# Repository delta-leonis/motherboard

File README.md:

# `motherboard`
> generic motherboard for robotic applications

The motherboard has seven identical slots for  modules which
are connected to a single CPU module slot which has up to seventy general purpose
inputs and outputs (GPIO), as well as , , and  communication buses.
The Motherboard also supplies each module with a direct battery connection
and additionally regulated  and  lines.

## Repository Contents
  * **/bom** - Bill of Materials csv files
  * **/design** - Autodesk Eagle design files & support library
  * **/gerbers** - Rendered Gerber RS_274x & Excellon files
  * **/images** - README image files
  * **/license** - License info

## Version History
  * [v1.0]() - Initial release - *January 2017*
  * [v1.1]() - Unreleased Version
  * [v1.2]() - Second production version - *April 2017*
  * v1.3 - Current version - *June 2017*

## Block Diagram

## Copyright

This work is licensed under a [Creative Commons Attribution-NonCommercial-ShareAlike 4.0 International License](https://creativecommons.org/licenses/by-nc-sa/4.0/legalcode)

**Attribution** — You must give [appropriate credit](/license/credit.md), provide a link to the license, and
[indicate if changes were made](https://wiki.creativecommons.org/License_Versions#Modifications_and_adaptations_must_be_marked_as_such).
You may do so in any reasonable manner, but not in any way that suggests the licensor endorses you or your use.

**NonCommercial** — You may not use the material for [commercial purposes]().

**ShareAlike** — If you remix, transform, or build upon the material, you must distribute your contributions under the [same license](https://creativecommons.org/licenses/by-nc-sa/4.0/legalcode) as the original.

If you have any questions or concerns on licensing, please contact [seifmegahed@me.com](mailto:seifmegahed@me.com)

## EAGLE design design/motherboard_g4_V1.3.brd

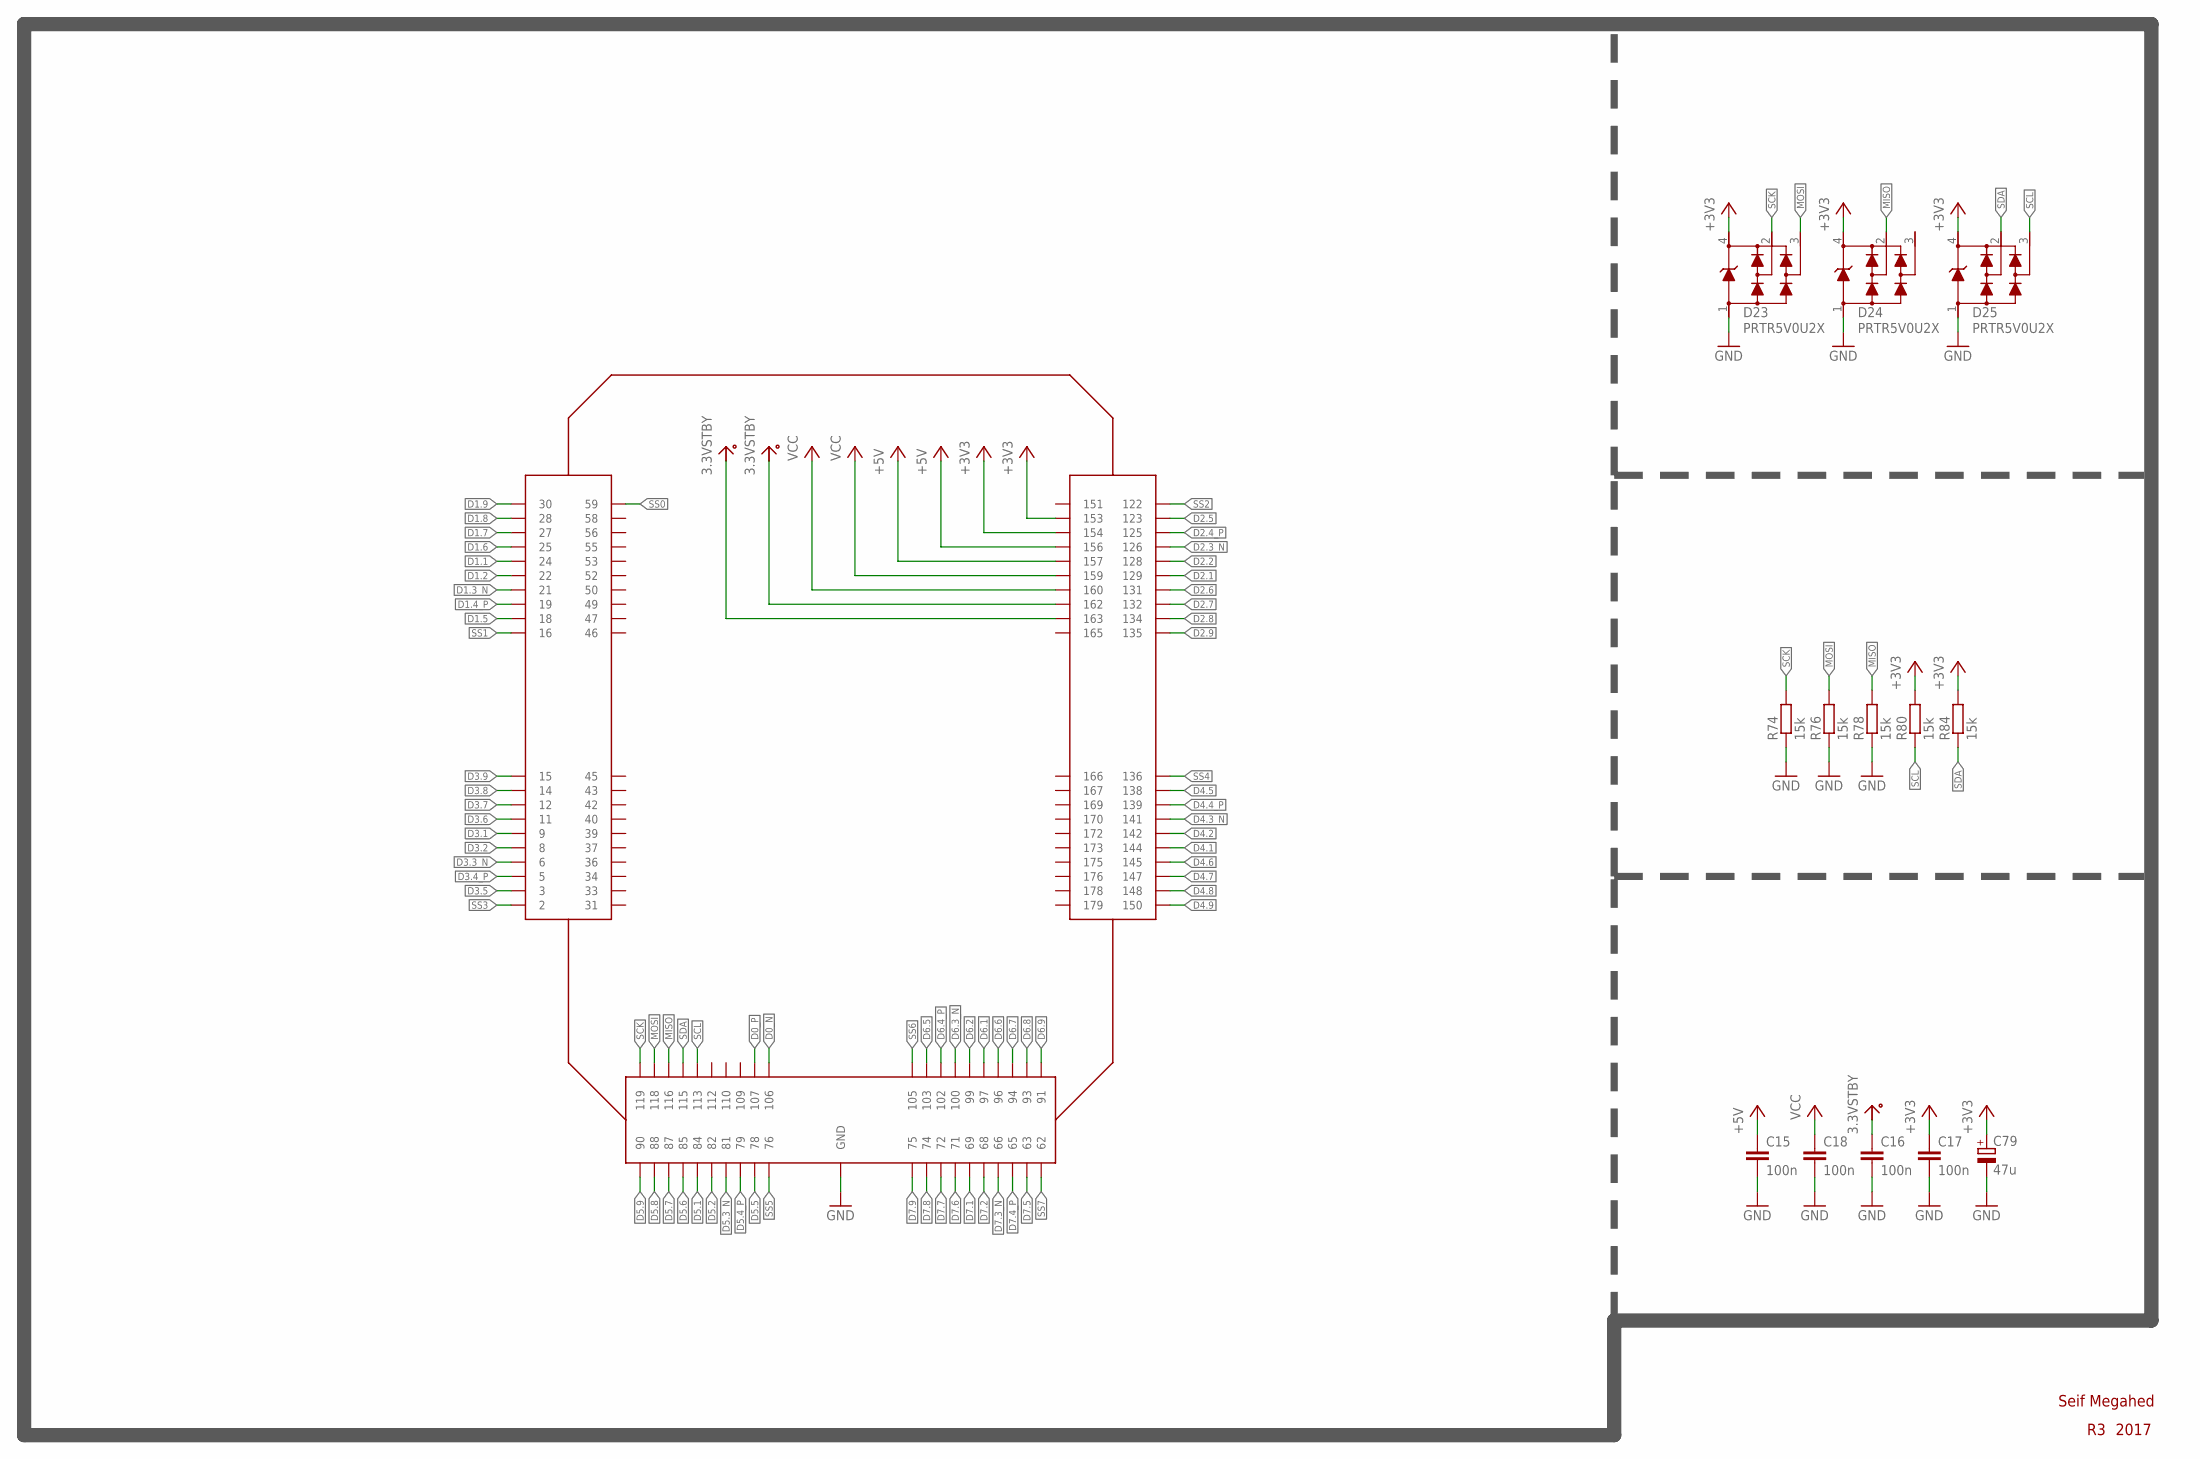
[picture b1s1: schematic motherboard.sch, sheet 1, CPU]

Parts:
C15, C16, C17, C18: 100n; CAP_0603
C79: 47u; PANASONIC_C
D23, D24, D25: PRTR5V0U2X; SOT143B
R74, R76, R78, R80, R84: 15k; RES_0603
U$4: SSH-G4-CPUDOCK; SSH-CPU-DOCK

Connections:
+3V3: C17.1, C79.+, D23.4, D24.4, D25.4, R80.2, R84.2, U$4.153, U$4.154; also elsewhere on the board
+5V: C15.1, U$4.156, U$4.157; also elsewhere on the board
D0_N: U$4.106; also elsewhere on the board
D0_P: U$4.107; also elsewhere on the board
D1.1: U$4.24; also elsewhere on the board
D1.2: U$4.22; also elsewhere on the board
D1.3_N: U$4.21; also elsewhere on the board
D1.4_P: U$4.19; also elsewhere on the board
D1.5: U$4.18; also elsewhere on the board
D1.6: U$4.25; also elsewhere on the board
D1.7: U$4.27; also elsewhere on the board
D1.8: U$4.28; also elsewhere on the board
D1.9: U$4.30; also elsewhere on the board
D2.1: U$4.129; also elsewhere on the board
D2.2: U$4.128; also elsewhere on the board
D2.3_N: U$4.126; also elsewhere on the board
D2.4_P: U$4.125; also elsewhere on the board
D2.5: U$4.123; also elsewhere on the board
D2.6: U$4.131; also elsewhere on the board
D2.7: U$4.132; also elsewhere on the board
D2.8: U$4.134; also elsewhere on the board
D2.9: U$4.135; also elsewhere on the board
D3.1: U$4.9; also elsewhere on the board
D3.2: U$4.8; also elsewhere on the board
D3.3_N: U$4.6; also elsewhere on the board
D3.4_P: U$4.5; also elsewhere on the board
D3.5: U$4.3; also elsewhere on the board
D3.6: U$4.11; also elsewhere on the board
D3.7: U$4.12; also elsewhere on the board
D3.8: U$4.14; also elsewhere on the board
D3.9: U$4.15; also elsewhere on the board
D4.1: U$4.144; also elsewhere on the board
D4.2: U$4.142; also elsewhere on the board
D4.3_N: U$4.141; also elsewhere on the board
D4.4_P: U$4.139; also elsewhere on the board
D4.5: U$4.138; also elsewhere on the board
D4.6: U$4.145; also elsewhere on the board
D4.7: U$4.147; also elsewhere on the board
D4.8: U$4.148; also elsewhere on the board
D4.9: U$4.150; also elsewhere on the board
D5.1: U$4.84; also elsewhere on the board
D5.2: U$4.82; also elsewhere on the board
D5.3_N: U$4.81; also elsewhere on the board
D5.4_P: U$4.79; also elsewhere on the board
D5.5: U$4.78; also elsewhere on the board
D5.6: U$4.85; also elsewhere on the board
D5.7: U$4.87; also elsewhere on the board
D5.8: U$4.88; also elsewhere on the board
D5.9: U$4.90; also elsewhere on the board
D6.1: U$4.97; also elsewhere on the board
D6.2: U$4.99; also elsewhere on the board
D6.3_N: U$4.100; also elsewhere on the board
D6.4_P: U$4.102; also elsewhere on the board
D6.5: U$4.103; also elsewhere on the board
D6.6: U$4.96; also elsewhere on the board
D6.7: U$4.94; also elsewhere on the board
D6.8: U$4.93; also elsewhere on the board
D6.9: U$4.91; also elsewhere on the board
D7.1: U$4.69; also elsewhere on the board
D7.2: U$4.68; also elsewhere on the board
D7.3_N: U$4.66; also elsewhere on the board
D7.4_P: U$4.65; also elsewhere on the board
D7.5: U$4.63; also elsewhere on the board
D7.6: U$4.71; also elsewhere on the board
D7.7: U$4.72; also elsewhere on the board
D7.8: U$4.74; also elsewhere on the board
D7.9: U$4.75; also elsewhere on the board
GND: C15.2, C16.2, C17.2, C18.2, C79.-, D23.1, D24.1, D25.1, R74.1, R76.1, R78.1, U$4.1 (GND), U$4.4 (GND), U$4.7 (GND), U$4.10 (GND), U$4.13 (GND), U$4.17 (GND), U$4.20 (GND), U$4.23 (GND), U$4.26 (GND), U$4.29 (GND), U$4.32 (GND), U$4.35 (GND), U$4.38 (GND), U$4.41 (GND), U$4.44 (GND), U$4.48 (GND), U$4.51 (GND), U$4.54 (GND), U$4.57 (GND), U$4.60 (GND), U$4.61 (GND), U$4.64 (GND), U$4.67 (GND), U$4.70 (GND), U$4.73 (GND), U$4.77 (GND), U$4.80 (GND), U$4.83 (GND), U$4.86 (GND), U$4.89 (GND), U$4.92 (GND), U$4.95 (GND), U$4.98 (GND), U$4.101 (GND), U$4.104 (GND), U$4.108 (GND), U$4.111 (GND), U$4.114 (GND), U$4.117 (GND), U$4.120 (GND), U$4.121 (GND), U$4.124 (GND), U$4.127 (GND), U$4.130 (GND), U$4.133 (GND), U$4.137 (GND), U$4.140 (GND), U$4.143 (GND), U$4.146 (GND), U$4.149 (GND), U$4.152 (GND), U$4.155 (GND), U$4.158 (GND), U$4.161 (GND), U$4.164 (GND), U$4.168 (GND), U$4.171 (GND), U$4.174 (GND), U$4.177 (GND), U$4.180 (GND), U$4.P$1 (GND), U$4.P$2 (GND), U$4.P$3 (GND), U$4.P$4 (GND), U$4.P$23 (GND), U$4.P$24 (GND); also elsewhere on the board
MISO: D24.2, R78.2, U$4.116; also elsewhere on the board
MOSI: D23.3, R76.2, U$4.118; also elsewhere on the board
SCK: D23.2, R74.2, U$4.119; also elsewhere on the board
SCL: D25.3, R80.1, U$4.113; also elsewhere on the board
SDA: D25.2, R84.1, U$4.115; also elsewhere on the board
SS0: U$4.59; also elsewhere on the board
SS1: U$4.16; also elsewhere on the board
SS2: U$4.122; also elsewhere on the board
SS3: U$4.2; also elsewhere on the board
SS4: U$4.136; also elsewhere on the board
SS5: U$4.76; also elsewhere on the board
SS6: U$4.105; also elsewhere on the board
SS7: U$4.62; also elsewhere on the board
STDBY3V3: C16.1, U$4.162, U$4.163
VCC: C18.1, U$4.159, U$4.160; also elsewhere on the board

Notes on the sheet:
Seif Megahed
2017

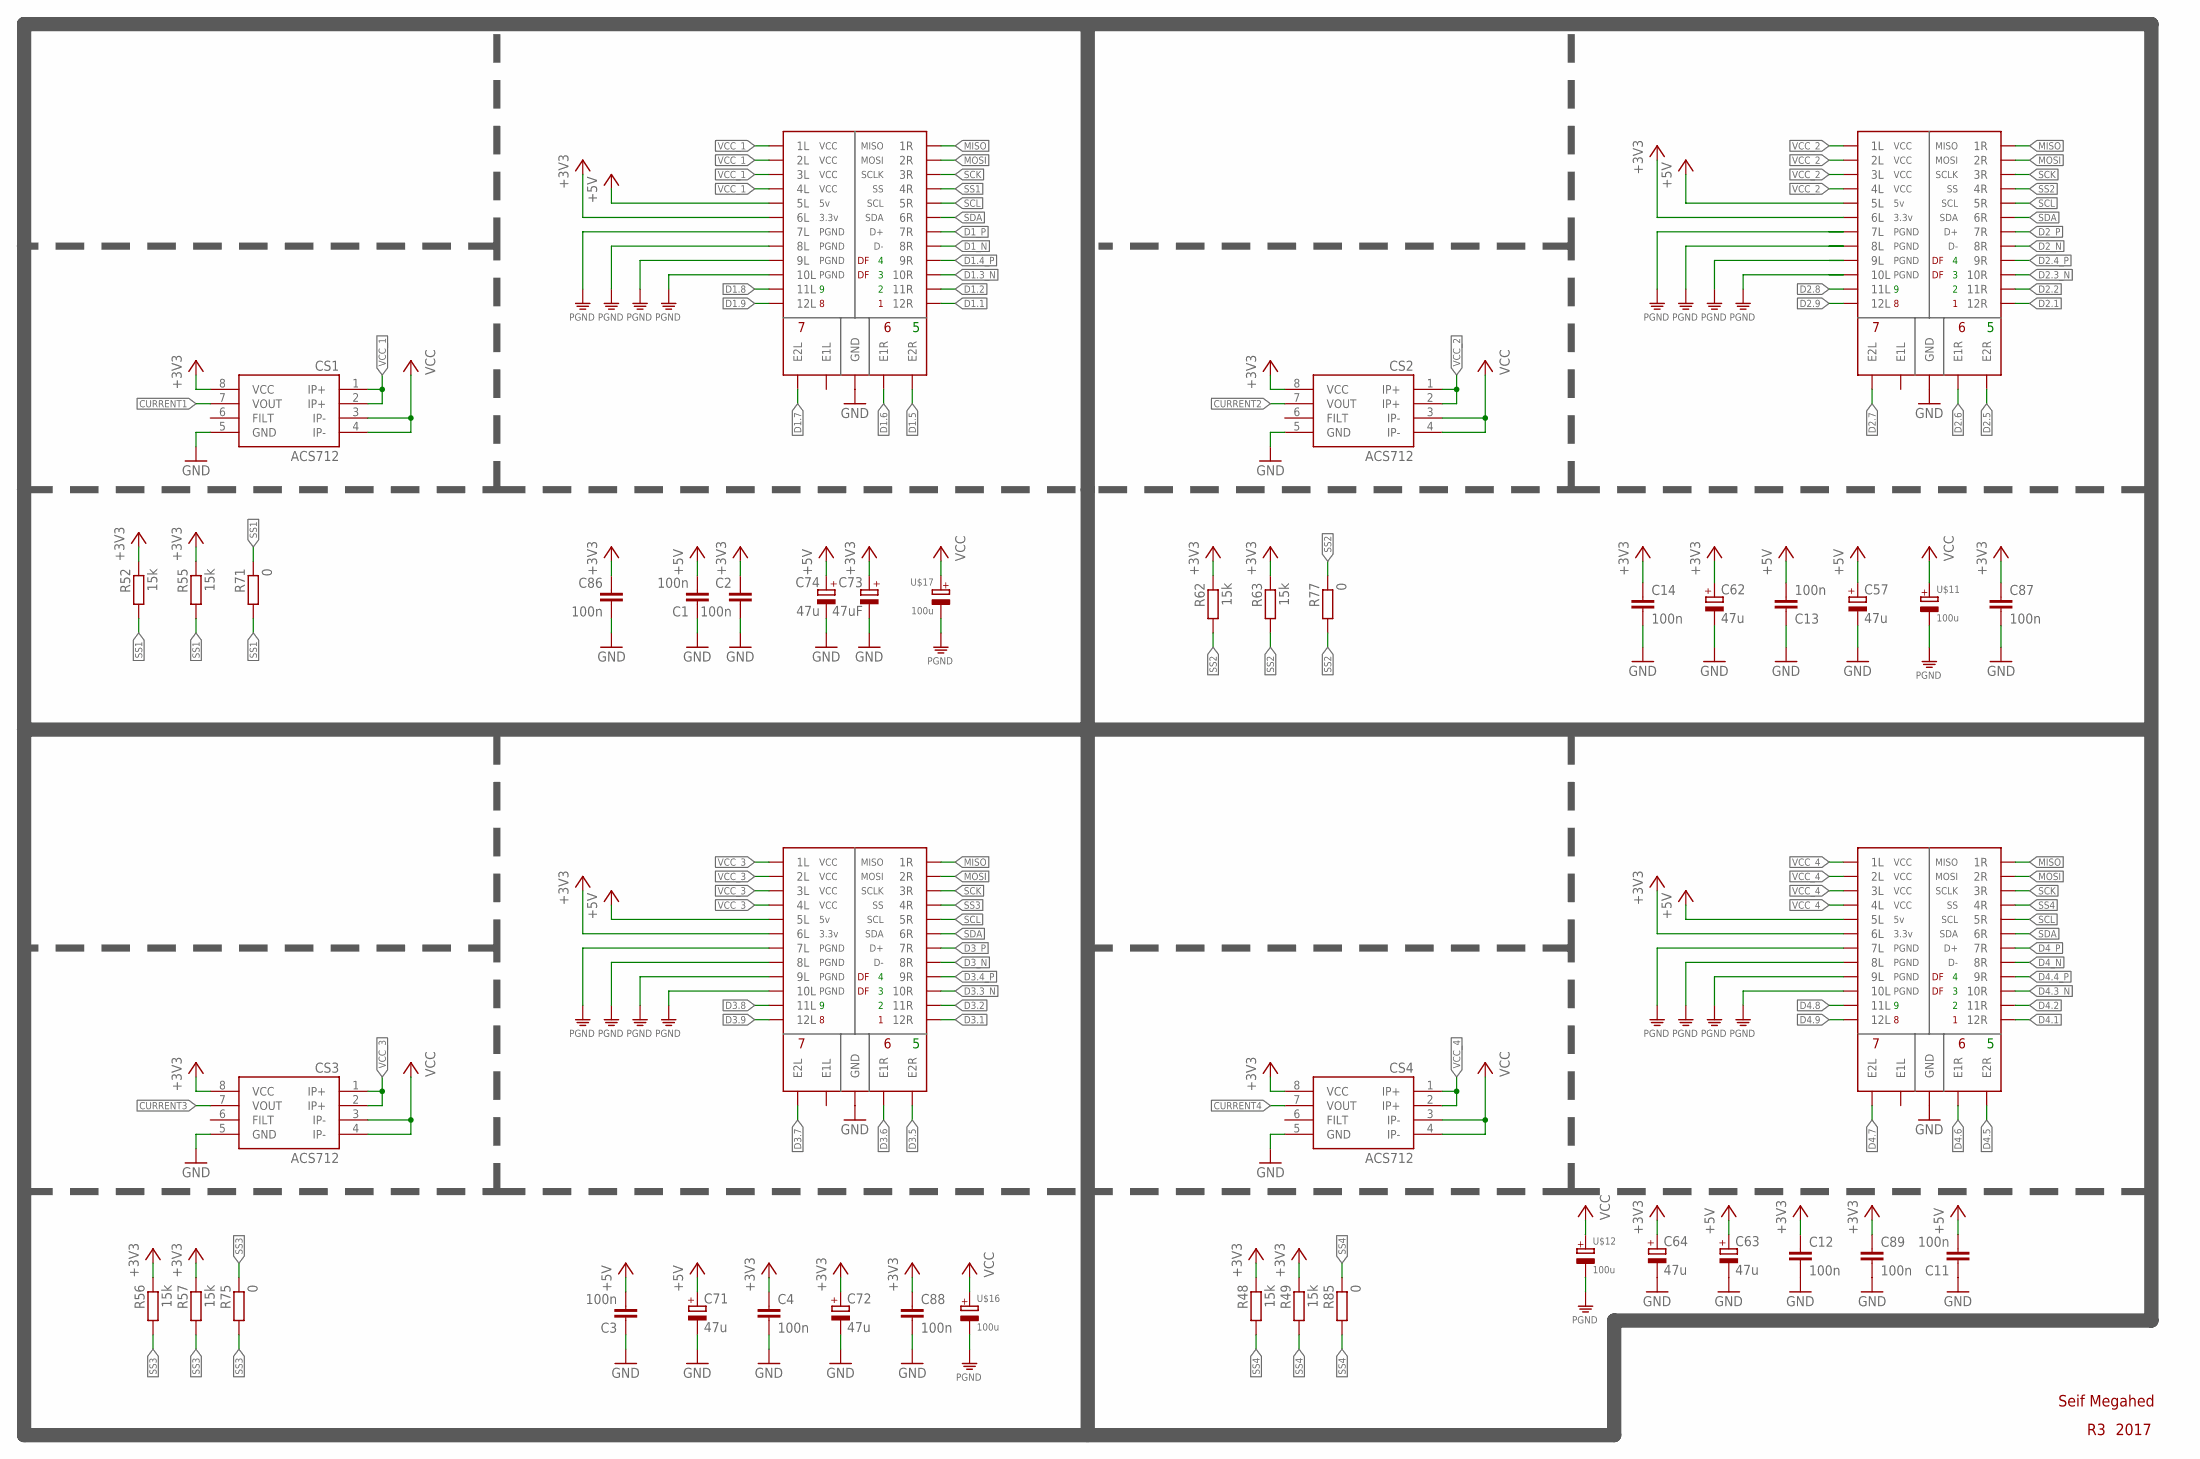
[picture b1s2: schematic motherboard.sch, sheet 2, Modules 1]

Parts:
C1, C2, C3, C4, C11, C12, C13, C14, C86, C87, C88, C89: 100n; CAP_0603
C57, C62, C63, C64, C71, C72, C74: 47u; PANASONIC_C
C73: 47uF; PANASONIC_C
CS1, CS2, CS3, CS4: ACS712; SO08
R48, R49, R52, R55, R56, R57, R62, R63: 15k; RES_0603
R71, R75, R77, R85: 0; RES_0603
U$5, U$6, U$7, U$8: SSH-G4-MODULEDOCK; SSH-G4-DOCK
U$11, U$12, U$16, U$17: 100u; AE_CAP_D

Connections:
+3V3: C2.1, C4.1, C12.1, C14.1, C62.+, C64.+, C72.+, C73.+, C86.1, C87.1, C88.1, C89.1, CS1.8 (VCC), CS2.8 (VCC), CS3.8 (VCC), CS4.8 (VCC), R48.1, R49.1, R52.1, R55.1, R56.1, R57.1, R62.1, R63.1, U$5.9SL (6L), U$6.9SL (6L), U$7.9SL (6L), U$8.9SL (6L); also elsewhere on the board
+5V: C1.2, C3.2, C11.2, C13.2, C57.+, C63.+, C71.+, C74.+, U$5.8SL (5L), U$6.8SL (5L), U$7.8SL (5L), U$8.8SL (5L); also elsewhere on the board
CURRENT1: CS1.7 (VOUT); also elsewhere on the board
CURRENT2: CS2.7 (VOUT); also elsewhere on the board
CURRENT3: CS3.7 (VOUT); also elsewhere on the board
CURRENT4: CS4.7 (VOUT); also elsewhere on the board
D1.1: U$7.21SR (12R); also elsewhere on the board
D1.2: U$7.20SR (11R); also elsewhere on the board
D1.3_N: U$7.18SR (10R); also elsewhere on the board
D1.4_P: U$7.17SR (9R); also elsewhere on the board
D1.5: U$7.12ER (E2R); also elsewhere on the board
D1.6: U$7.11ER (E1R); also elsewhere on the board
D1.7: U$7.12EL (E2L); also elsewhere on the board
D1.8: U$7.20SL (11L); also elsewhere on the board
D1.9: U$7.21SL (12L); also elsewhere on the board
D1_N: U$7.15SR (8R); also elsewhere on the board
D1_P: U$7.14SR (7R); also elsewhere on the board
D2.1: U$8.21SR (12R); also elsewhere on the board
D2.2: U$8.20SR (11R); also elsewhere on the board
D2.3_N: U$8.18SR (10R); also elsewhere on the board
D2.4_P: U$8.17SR (9R); also elsewhere on the board
D2.5: U$8.12ER (E2R); also elsewhere on the board
D2.6: U$8.11ER (E1R); also elsewhere on the board
D2.7: U$8.12EL (E2L); also elsewhere on the board
D2.8: U$8.20SL (11L); also elsewhere on the board
D2.9: U$8.21SL (12L); also elsewhere on the board
D2_N: U$8.15SR (8R); also elsewhere on the board
D2_P: U$8.14SR (7R); also elsewhere on the board
D3.1: U$5.21SR (12R); also elsewhere on the board
D3.2: U$5.20SR (11R); also elsewhere on the board
D3.3_N: U$5.18SR (10R); also elsewhere on the board
D3.4_P: U$5.17SR (9R); also elsewhere on the board
D3.5: U$5.12ER (E2R); also elsewhere on the board
D3.6: U$5.11ER (E1R); also elsewhere on the board
D3.7: U$5.12EL (E2L); also elsewhere on the board
D3.8: U$5.20SL (11L); also elsewhere on the board
D3.9: U$5.21SL (12L); also elsewhere on the board
D3_N: U$5.15SR (8R); also elsewhere on the board
D3_P: U$5.14SR (7R); also elsewhere on the board
D4.1: U$6.21SR (12R); also elsewhere on the board
D4.2: U$6.20SR (11R); also elsewhere on the board
D4.3_N: U$6.18SR (10R); also elsewhere on the board
D4.4_P: U$6.17SR (9R); also elsewhere on the board
D4.5: U$6.12ER (E2R); also elsewhere on the board
D4.6: U$6.11ER (E1R); also elsewhere on the board
D4.7: U$6.12EL (E2L); also elsewhere on the board
D4.8: U$6.20SL (11L); also elsewhere on the board
D4.9: U$6.21SL (12L); also elsewhere on the board
D4_N: U$6.15SR (8R); also elsewhere on the board
D4_P: U$6.14SR (7R); also elsewhere on the board
GND: C1.1, C2.2, C3.1, C4.2, C11.1, C12.2, C13.1, C14.2, C57.-, C62.-, C63.-, C64.-, C71.-, C72.-, C73.-, C74.-, C86.2, C87.2, C88.2, C89.2, CS1.5 (GND), CS2.5 (GND), CS3.5 (GND), CS4.5 (GND), U$5.1GL (GND), U$5.1GR (GND), U$5.4GL (GND), U$5.4GR (GND), U$5.7GL (GND), U$5.7GR (GND), U$5.10GL (GND), U$5.10GR (GND), U$5.13GL (GND), U$5.13GR (GND), U$5.16GL (GND), U$5.16GR (GND), U$5.19GL (GND), U$5.19GR (GND), U$5.22GL (GND), U$5.22GR (GND), U$6.1GL (GND), U$6.1GR (GND), U$6.4GL (GND), U$6.4GR (GND), U$6.7GL (GND), U$6.7GR (GND), U$6.10GL (GND), U$6.10GR (GND), U$6.13GL (GND), U$6.13GR (GND), U$6.16GL (GND), U$6.16GR (GND), U$6.19GL (GND), U$6.19GR (GND), U$6.22GL (GND), U$6.22GR (GND), U$7.1GL (GND), U$7.1GR (GND), U$7.4GL (GND), U$7.4GR (GND), U$7.7GL (GND), U$7.7GR (GND), U$7.10GL (GND), U$7.10GR (GND), U$7.13GL (GND), U$7.13GR (GND), U$7.16GL (GND), U$7.16GR (GND), U$7.19GL (GND), U$7.19GR (GND), U$7.22GL (GND), U$7.22GR (GND), U$8.1GL (GND), U$8.1GR (GND), U$8.4GL (GND), U$8.4GR (GND), U$8.7GL (GND), U$8.7GR (GND), U$8.10GL (GND), U$8.10GR (GND), U$8.13GL (GND), U$8.13GR (GND), U$8.16GL (GND), U$8.16GR (GND), U$8.19GL (GND), U$8.19GR (GND), U$8.22GL (GND), U$8.22GR (GND); also elsewhere on the board
MISO: U$5.2SR (1R), U$6.2SR (1R), U$7.2SR (1R), U$8.2SR (1R); also elsewhere on the board
MOSI: U$5.3SR (2R), U$6.3SR (2R), U$7.3SR (2R), U$8.3SR (2R); also elsewhere on the board
PGND: U$7.14SL (7L), U$7.15SL (8L), U$7.17SL (9L), U$7.18SL (10L), U$8.14SL (7L), U$8.15SL (8L), U$8.17SL (9L), U$8.18SL (10L), U$11.-, U$12.-, U$16.-, U$17.-; also elsewhere on the board
SCK: U$5.5SR (3R), U$6.5SR (3R), U$7.5SR (3R), U$8.5SR (3R); also elsewhere on the board
SCL: U$5.8SR (5R), U$6.8SR (5R), U$7.8SR (5R), U$8.8SR (5R); also elsewhere on the board
SDA: U$5.9SR (6R), U$6.9SR (6R), U$7.9SR (6R), U$8.9SR (6R); also elsewhere on the board
SS1: R52.2, R55.2, R71.1, R71.2, U$7.6SR (4R); also elsewhere on the board
SS2: R62.2, R63.2, R77.1, R77.2, U$8.6SR (4R); also elsewhere on the board
SS3: R56.2, R57.2, R75.1, R75.2, U$5.6SR (4R); also elsewhere on the board
SS4: R48.2, R49.2, R85.1, R85.2, U$6.6SR (4R); also elsewhere on the board
VCC: CS1.3 (IP-), CS1.4 (IP-), CS2.3 (IP-), CS2.4 (IP-), CS3.3 (IP-), CS3.4 (IP-), CS4.3 (IP-), CS4.4 (IP-), U$11.+, U$12.+, U$16.+, U$17.+; also elsewhere on the board
VCC_1: CS1.1 (IP+), CS1.2 (IP+), U$7.2SL (1L), U$7.3SL (2L), U$7.5SL (3L), U$7.6SL (4L)
VCC_2: CS2.1 (IP+), CS2.2 (IP+), U$8.2SL (1L), U$8.3SL (2L), U$8.5SL (3L), U$8.6SL (4L)
VCC_3: CS3.1 (IP+), CS3.2 (IP+), U$5.2SL (1L), U$5.3SL (2L), U$5.5SL (3L), U$5.6SL (4L)
VCC_4: CS4.1 (IP+), CS4.2 (IP+), U$6.2SL (1L), U$6.3SL (2L), U$6.5SL (3L), U$6.6SL (4L)

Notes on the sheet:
Seif Megahed
2017

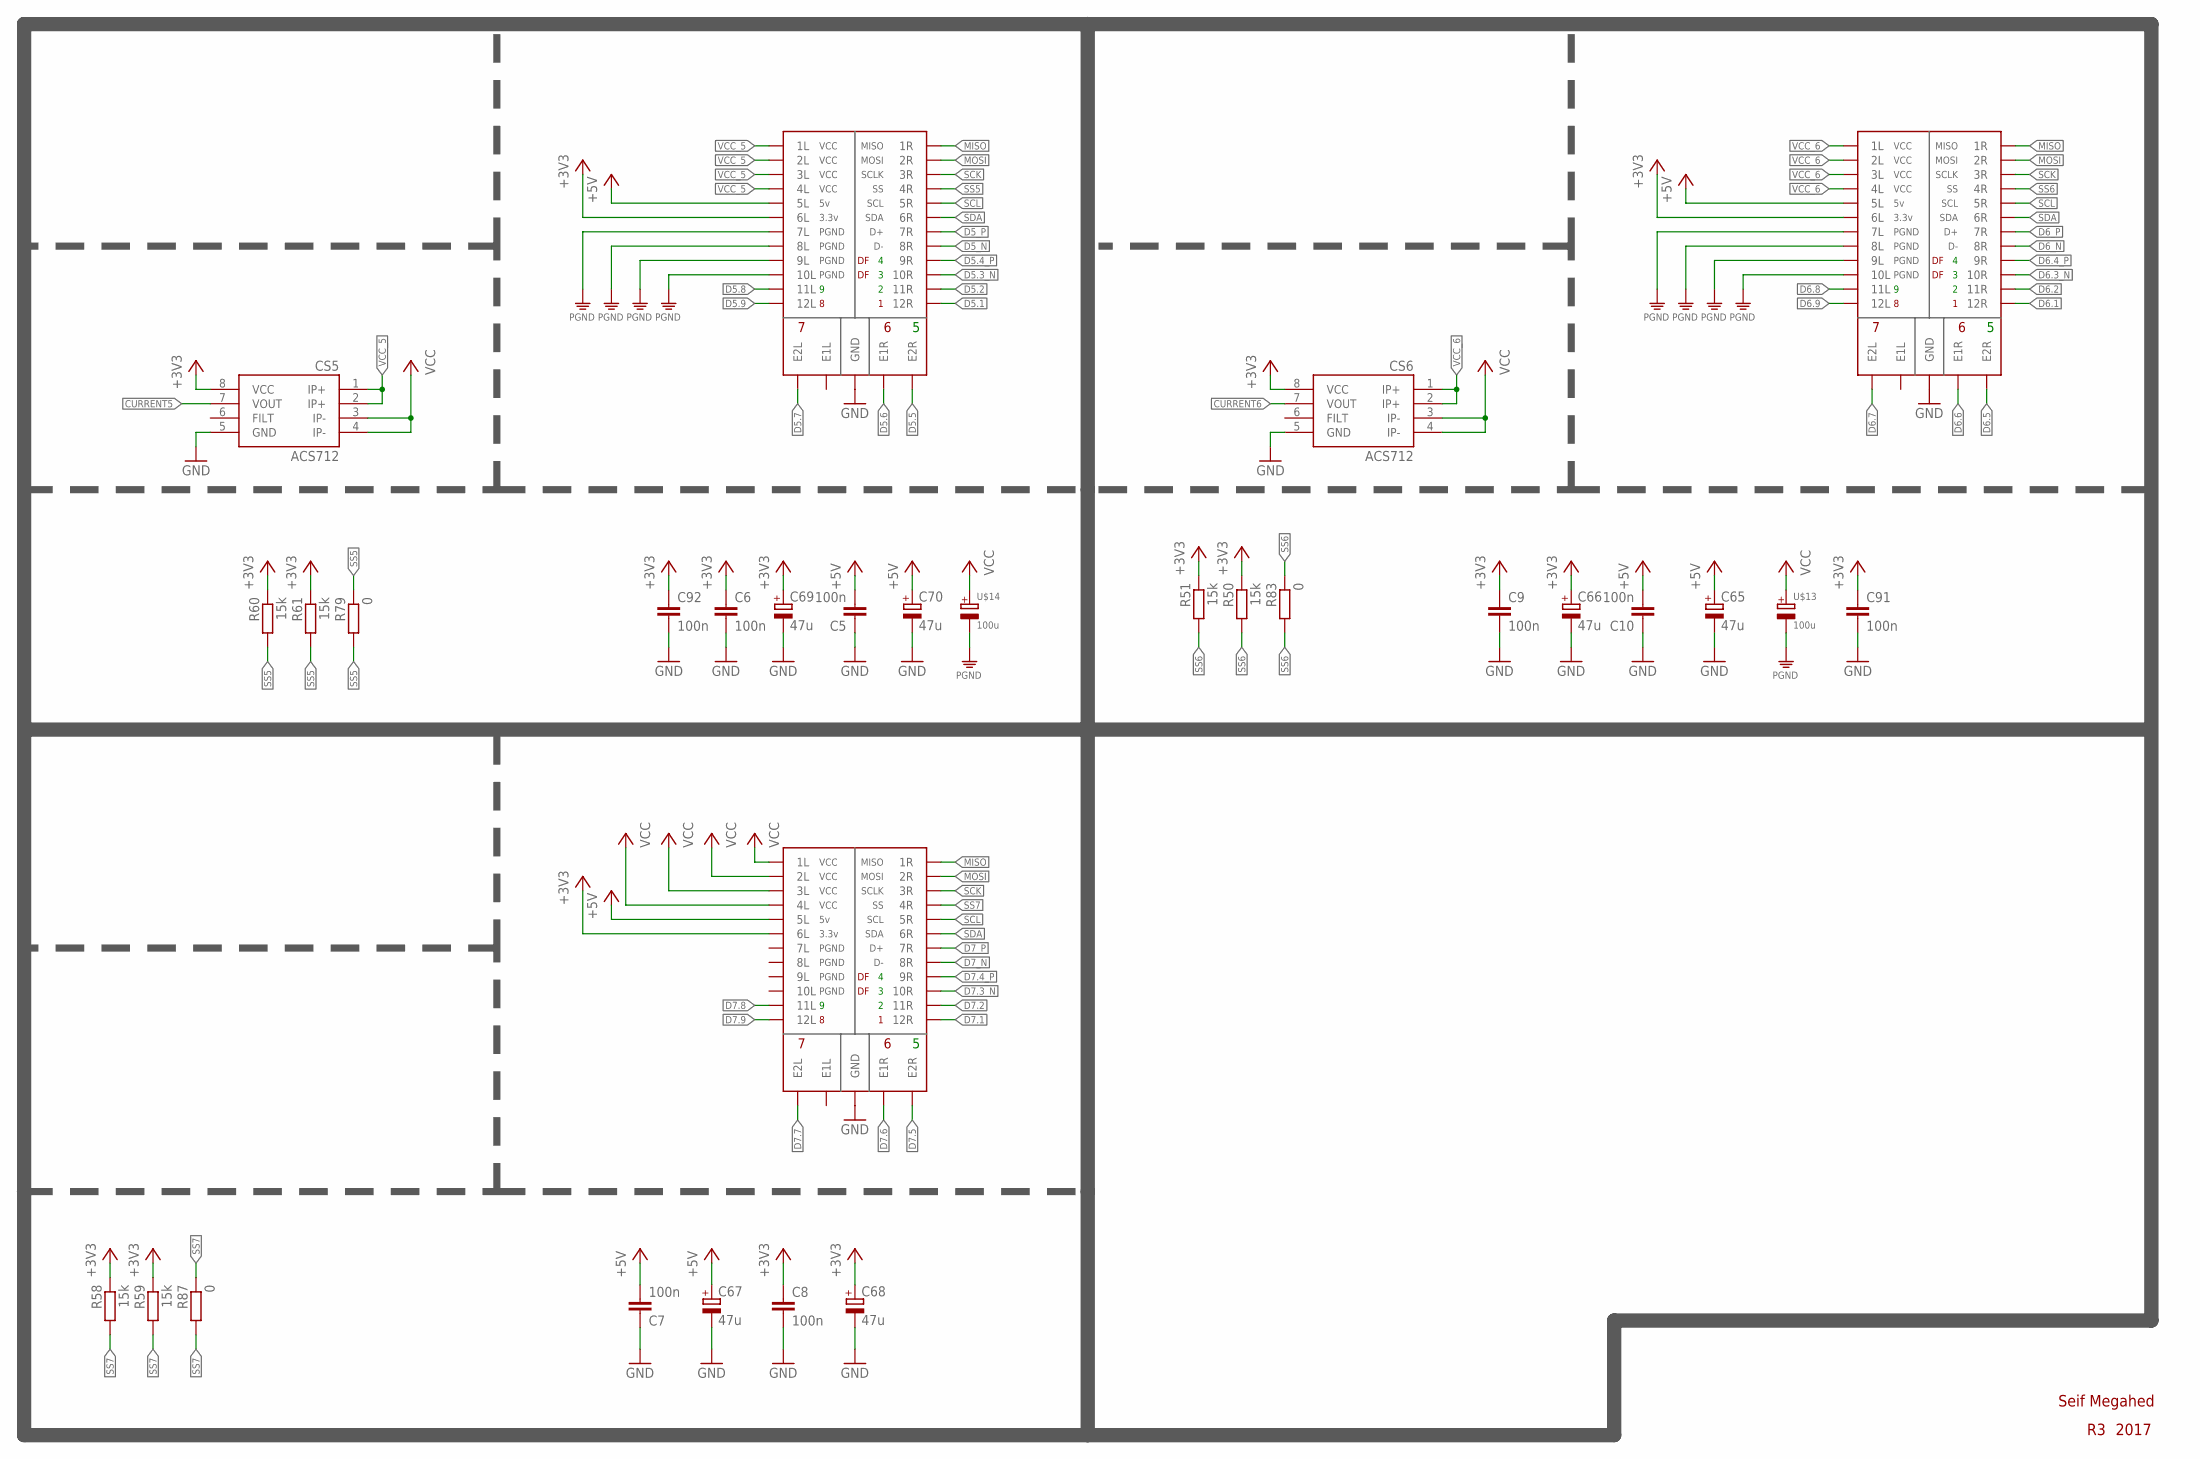
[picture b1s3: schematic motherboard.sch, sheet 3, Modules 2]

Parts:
C5, C6, C7, C8, C9, C10, C91, C92: 100n; CAP_0603
C65, C66, C67, C68, C69, C70: 47u; PANASONIC_C
CS5, CS6: ACS712; SO08
R50, R51, R58, R59, R60, R61: 15k; RES_0603
R79, R83, R87: 0; RES_0603
U$1, U$2: SSH-G4-MODULEDOCK; SSH-G4-DOCK
U$3: SSH-G4-MODULESENSOR_DOCK; SSH-SENSOR-G4-DOCK
U$13, U$14: 100u; AE_CAP_D

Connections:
+3V3: C6.1, C8.1, C9.1, C66.+, C68.+, C69.+, C91.1, C92.1, CS5.8 (VCC), CS6.8 (VCC), R50.1, R51.1, R58.1, R59.1, R60.1, R61.1, U$1.9SL (6L), U$2.9SL (6L), U$3.9SL (6L); also elsewhere on the board
+5V: C5.2, C7.2, C10.2, C65.+, C67.+, C70.+, U$1.8SL (5L), U$2.8SL (5L), U$3.8SL (5L); also elsewhere on the board
CURRENT5: CS5.7 (VOUT); also elsewhere on the board
CURRENT6: CS6.7 (VOUT); also elsewhere on the board
D5.1: U$1.21SR (12R); also elsewhere on the board
D5.2: U$1.20SR (11R); also elsewhere on the board
D5.3_N: U$1.18SR (10R); also elsewhere on the board
D5.4_P: U$1.17SR (9R); also elsewhere on the board
D5.5: U$1.12ER (E2R); also elsewhere on the board
D5.6: U$1.11ER (E1R); also elsewhere on the board
D5.7: U$1.12EL (E2L); also elsewhere on the board
D5.8: U$1.20SL (11L); also elsewhere on the board
D5.9: U$1.21SL (12L); also elsewhere on the board
D5_N: U$1.15SR (8R); also elsewhere on the board
D5_P: U$1.14SR (7R); also elsewhere on the board
D6.1: U$2.21SR (12R); also elsewhere on the board
D6.2: U$2.20SR (11R); also elsewhere on the board
D6.3_N: U$2.18SR (10R); also elsewhere on the board
D6.4_P: U$2.17SR (9R); also elsewhere on the board
D6.5: U$2.12ER (E2R); also elsewhere on the board
D6.6: U$2.11ER (E1R); also elsewhere on the board
D6.7: U$2.12EL (E2L); also elsewhere on the board
D6.8: U$2.20SL (11L); also elsewhere on the board
D6.9: U$2.21SL (12L); also elsewhere on the board
D6_N: U$2.15SR (8R); also elsewhere on the board
D6_P: U$2.14SR (7R); also elsewhere on the board
D7.1: U$3.21SR (12R); also elsewhere on the board
D7.2: U$3.20SR (11R); also elsewhere on the board
D7.3_N: U$3.18SR (10R); also elsewhere on the board
D7.4_P: U$3.17SR (9R); also elsewhere on the board
D7.5: U$3.12ER (E2R); also elsewhere on the board
D7.6: U$3.11ER (E1R); also elsewhere on the board
D7.7: U$3.12EL (E2L); also elsewhere on the board
D7.8: U$3.20SL (11L); also elsewhere on the board
D7.9: U$3.21SL (12L); also elsewhere on the board
D7_N: U$3.15SR (8R); also elsewhere on the board
D7_P: U$3.14SR (7R); also elsewhere on the board
GND: C5.1, C6.2, C7.1, C8.2, C9.2, C10.1, C65.-, C66.-, C67.-, C68.-, C69.-, C70.-, C91.2, C92.2, CS5.5 (GND), CS6.5 (GND), U$1.1GL (GND), U$1.1GR (GND), U$1.4GL (GND), U$1.4GR (GND), U$1.7GL (GND), U$1.7GR (GND), U$1.10GL (GND), U$1.10GR (GND), U$1.13GL (GND), U$1.13GR (GND), U$1.16GL (GND), U$1.16GR (GND), U$1.19GL (GND), U$1.19GR (GND), U$1.22GL (GND), U$1.22GR (GND), U$2.1GL (GND), U$2.1GR (GND), U$2.4GL (GND), U$2.4GR (GND), U$2.7GL (GND), U$2.7GR (GND), U$2.10GL (GND), U$2.10GR (GND), U$2.13GL (GND), U$2.13GR (GND), U$2.16GL (GND), U$2.16GR (GND), U$2.19GL (GND), U$2.19GR (GND), U$2.22GL (GND), U$2.22GR (GND), U$3.1GL (GND), U$3.1GR (GND), U$3.4GL (GND), U$3.4GR (GND), U$3.7GL (GND), U$3.7GR (GND), U$3.10GL (GND), U$3.10GR (GND), U$3.13GL (GND), U$3.13GR (GND), U$3.16GL (GND), U$3.16GR (GND), U$3.19GL (GND), U$3.19GR (GND), U$3.22GL (GND), U$3.22GR (GND); also elsewhere on the board
MISO: U$1.2SR (1R), U$2.2SR (1R), U$3.2SR (1R); also elsewhere on the board
MOSI: U$1.3SR (2R), U$2.3SR (2R), U$3.3SR (2R); also elsewhere on the board
PGND: U$13.-, U$14.-; also elsewhere on the board
SCK: U$1.5SR (3R), U$2.5SR (3R), U$3.5SR (3R); also elsewhere on the board
SCL: U$1.8SR (5R), U$2.8SR (5R), U$3.8SR (5R); also elsewhere on the board
SDA: U$1.9SR (6R), U$2.9SR (6R), U$3.9SR (6R); also elsewhere on the board
SS5: R60.2, R61.2, R79.1, R79.2, U$1.6SR (4R); also elsewhere on the board
SS6: R50.2, R51.2, R83.1, R83.2, U$2.6SR (4R); also elsewhere on the board
SS7: R58.2, R59.2, R87.1, R87.2, U$3.6SR (4R); also elsewhere on the board
VCC: CS5.3 (IP-), CS5.4 (IP-), CS6.3 (IP-), CS6.4 (IP-), U$3.2SL (1L), U$3.3SL (2L), U$3.5SL (3L), U$3.6SL (4L), U$13.+, U$14.+; also elsewhere on the board
VCC_5: CS5.1 (IP+), CS5.2 (IP+), U$1.2SL (1L), U$1.3SL (2L), U$1.5SL (3L), U$1.6SL (4L)
VCC_6: CS6.1 (IP+), CS6.2 (IP+), U$2.2SL (1L), U$2.3SL (2L), U$2.5SL (3L), U$2.6SL (4L)

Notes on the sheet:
Seif Megahed
2017

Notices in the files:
README.md:
CC BY-NC-SA 4.0
parts and their libraries:
SparkFun-Aesthetics: Licensing: Creative Commons ShareAlike 4.0 International - https://creativecommons.org/licenses/by-sa/4.0
